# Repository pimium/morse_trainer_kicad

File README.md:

# Morse Trainer the Board

## Schematic

[Schematic as pdf-file](images/morse_trainer_sch.pdf)

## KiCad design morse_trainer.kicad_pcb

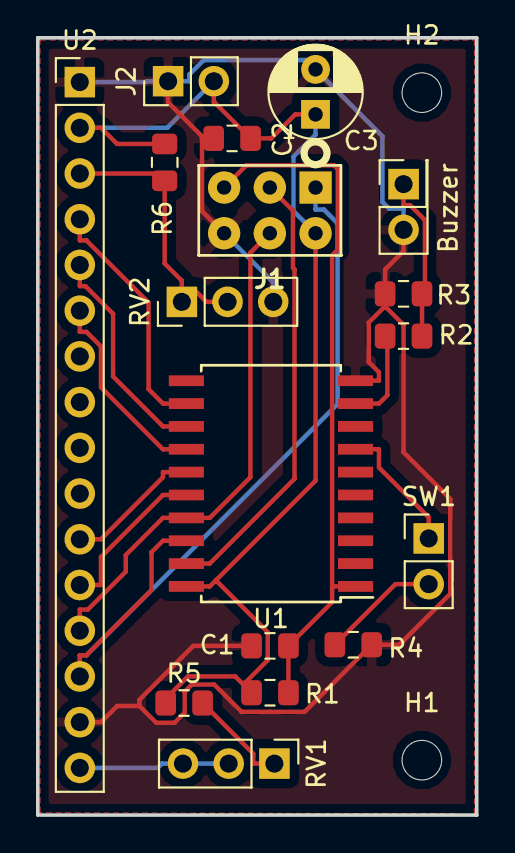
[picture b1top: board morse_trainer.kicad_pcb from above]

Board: 2 copper layers, 24.4 x 43.2 mm, 19 parts (0 on the bottom side), 18 nets.

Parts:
BZ1: Buzzer; PinSocket_2x01_P2.54mm_Vertical
C1, C2: 100n; C_0805_2012Metric_Pad1.15x1.40mm_HandSolder
C3: 100u; CP_Radial_D5.0mm_P2.50mm
H1, H2: MountingHole; MountingHole_2.2mm_M2
J1: AVR-ISP-6; ISP
J2: Conn_01x02; PinHeader_1x02_P2.54mm_Vertical
R1, R3: 1k; R_0805_2012Metric_Pad1.15x1.40mm_HandSolder
R2, R5: 100; R_0805_2012Metric_Pad1.15x1.40mm_HandSolder
R4: 470; R_0805_2012Metric_Pad1.15x1.40mm_HandSolder
R6: 100k; R_0805_2012Metric_Pad1.15x1.40mm_HandSolder
RV1, RV2: 1k; PinHeader_1x03_P2.54mm_Vertical
SW1: SW_Push; PinHeader_1x02_P2.54mm_Vertical
U1: ATtiny2313-20SU; SOIC-20W_7.5x12.8mm_P1.27mm
U2: RC1602A; PinHeader_1x16_P2.54mm_Vertical

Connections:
/DB4: U1.15, U2.11
/DB5: U1.16, U2.12
/DB6: J1.4, U1.17, U2.13
/DB7: J1.1, U1.18, U2.14
/E: U1.14, U2.6
/RS: U1.12, U2.4
/R\~W: U1.13, U2.5
/SCK: J1.3, U1.19
/~RST: C1.1, J1.5, R1.2, U1.1
GND: BZ1.2, C1.2, C2.2, C3.2, J1.6, J2.1, R3.2, R4.2, RV2.3, U1.10, U2.1, U2.15
unnamed: BZ1.1, R2.2, R3.1
unnamed: R2.1, U1.9
unnamed: R4.1, SW1.2
unnamed: R5.2, RV1.1
unnamed: R6.2, RV2.1, RV2.2, U2.3
unnamed: RV1.2, RV1.3, U2.16
unnamed: SW1.1, U1.7
VCC: C2.1, C3.1, J1.2, J2.2, R1.1, R5.1, R6.1, U1.20, U2.2

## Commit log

2019-09-25 Schematic done !
2019-10-02 Schematics done !
2020-06-03 add 2 10 pin connector to the schematic \n first version of the boad is done
2020-08-24 add pictures
2020-08-24 export pictures
